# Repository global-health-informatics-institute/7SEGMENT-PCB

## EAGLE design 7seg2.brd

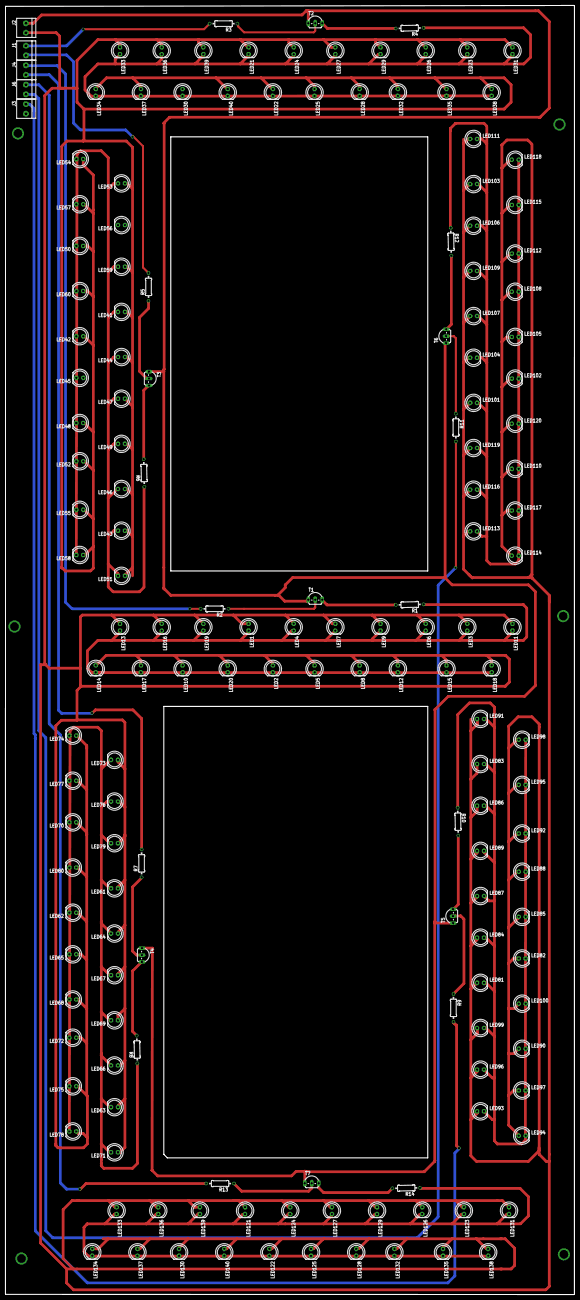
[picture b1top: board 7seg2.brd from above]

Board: 2 copper layers, 208.1 x 471.4 mm, 172 parts (0 on the bottom side), 3 nets.

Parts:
J1, J2, J3, J4, J6: 1X2-3.5MM
LED1, LED2, LED3, LED4, LED5, LED6, LED7, LED8, LED9, LED10, LED11, LED12, LED13, LED14, LED15, LED16, LED17, LED18, LED19, LED20, LED21, LED22, LED23, LED24, LED25, LED26, LED27, LED28, LED29, LED30, LED31, LED32, LED33, LED34, LED35, LED36, LED37, LED38, LED39, LED40, LED41, LED42, LED43, LED44, LED45, LED46, LED47, LED48, LED49, LED50, LED51, LED52, LED53, LED54, LED55, LED56, LED57, LED58, LED59, LED60, LED61, LED62, LED63, LED64, LED65, LED66, LED67, LED68, LED69, LED70, LED71, LED72, LED73, LED74, LED75, LED76, LED77, LED78, LED79, LED80, LED81, LED82, LED83, LED84, LED85, LED86, LED87, LED88, LED89, LED90, LED91, LED92, LED93, LED94, LED95, LED96, LED97, LED98, LED99, LED100, LED101, LED102, LED103, LED104, LED105, LED106, LED107, LED108, LED109, LED110, LED111, LED112, LED113, LED114, LED115, LED116, LED117, LED118, LED119, LED120, LED121, LED122, LED123, LED124, LED125, LED126, LED127, LED128, LED129, LED130, LED131, LED132, LED133, LED134, LED135, LED136, LED137, LED138, LED139, LED140: LED5MM
MGT2, MGT3, MGT4, MGT6, MGT8, MGT9: BEAGLEBONEBLACK_MOUNTING_HOLE
R1, R2, R3, R4, R5, R6, R7, R8, R9, R10, R11, R12, R13, R14: 0207/10
T1, T2, T3, T4, T5, T6, T7: 2N2222; TO92-EBC-OVAL

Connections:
unnamed: R2.1, T1.B
unnamed: R3.1, T2.B
unnamed: R11.1, T6.B

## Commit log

2019-11-25 this is the schmatic diagram for the pcb
2019-11-25 this is the board design
2019-11-25 this is the second version of the pcb
